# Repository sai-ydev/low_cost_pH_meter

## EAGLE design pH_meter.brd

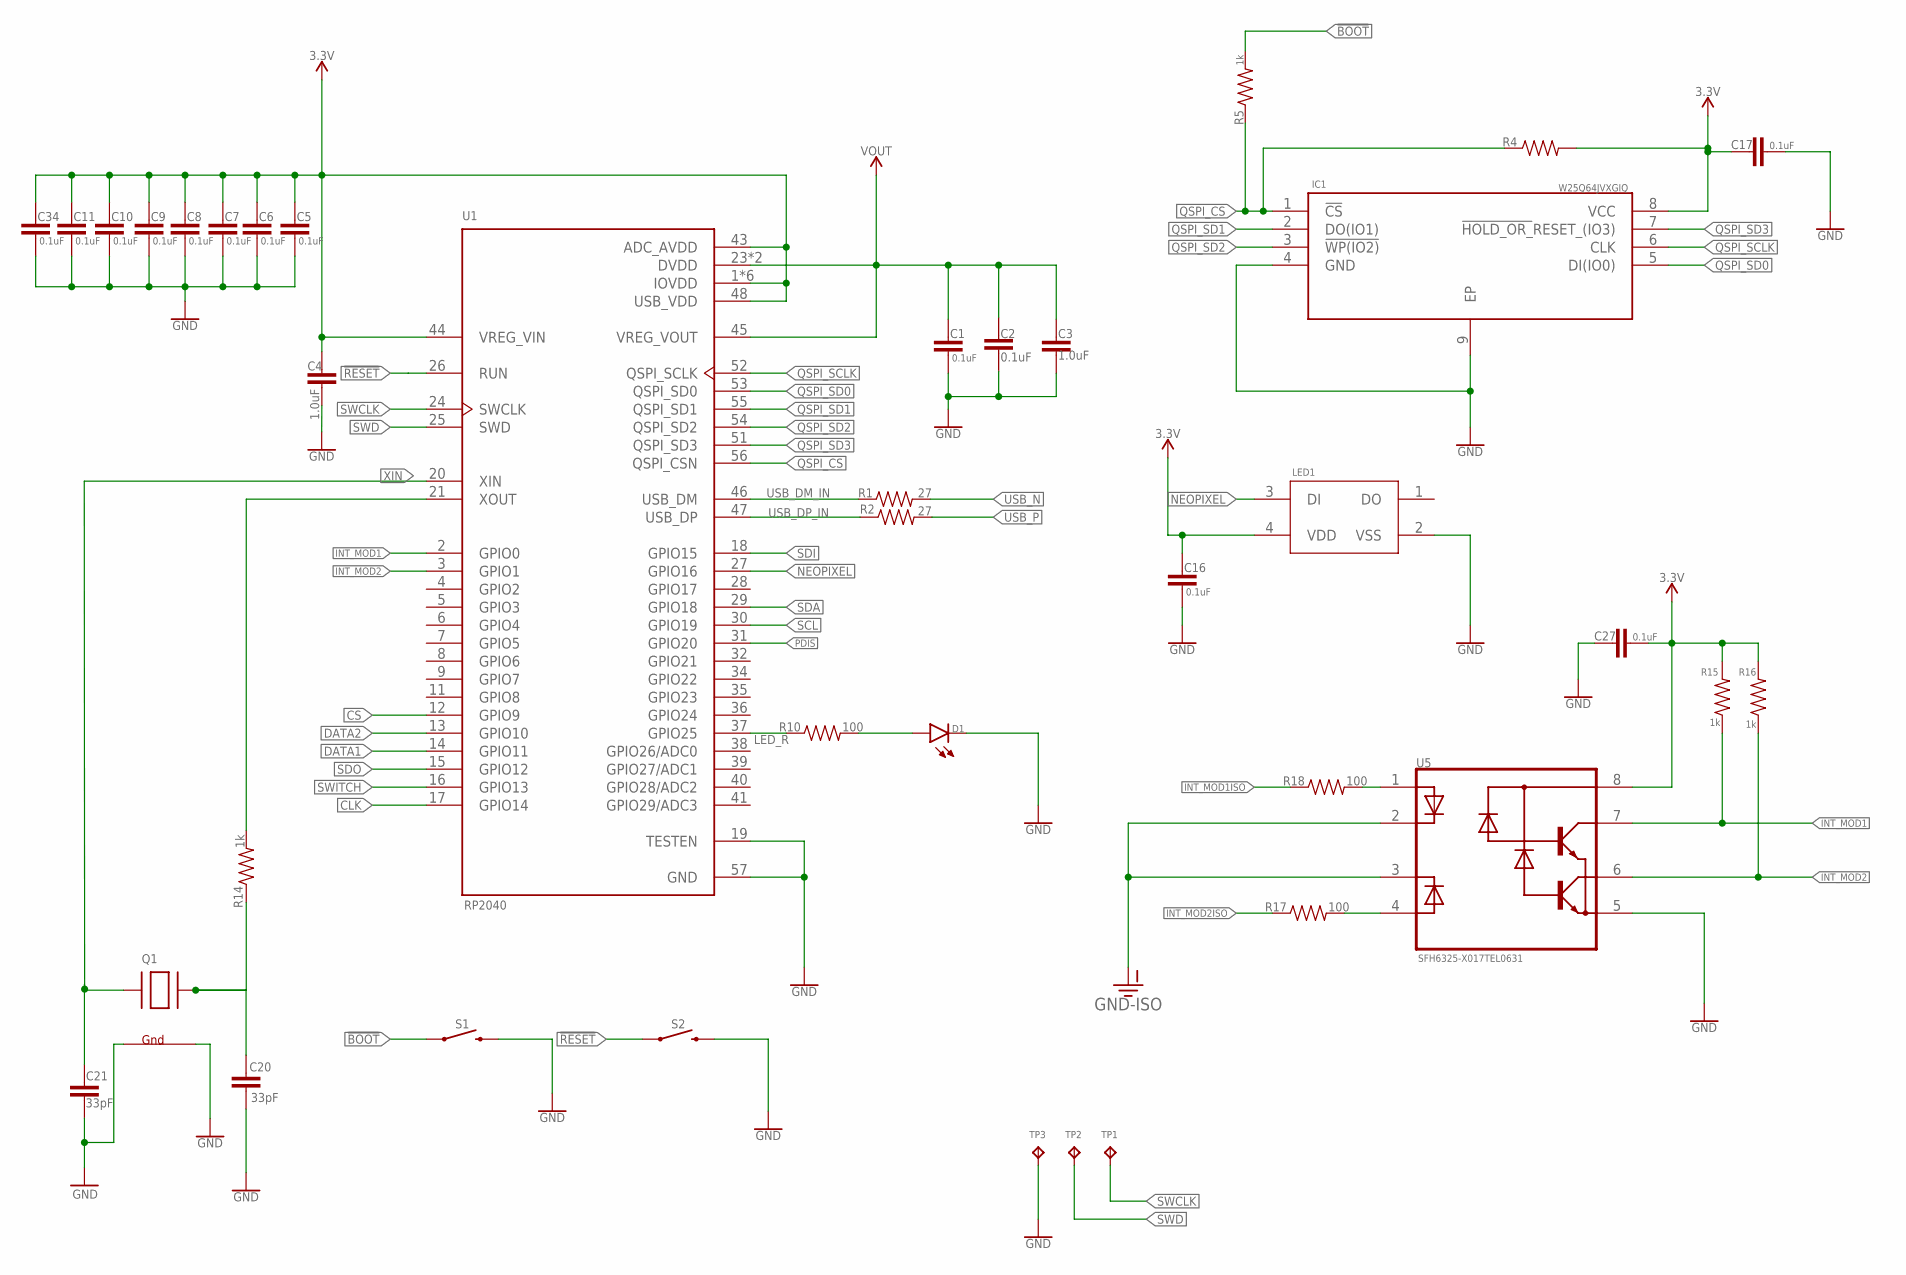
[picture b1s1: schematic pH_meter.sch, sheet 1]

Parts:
C1, C2, C5, C6, C7, C8, C9, C10, C11, C16, C17, C27, C34: 0.1uF; 0603
C3, C4: 1.0uF; 0603
C20, C21: 33pF; 0603
D1: LED0603; LED-0603
IC1: W25Q64JVXGIQ; SON80P400X400X50-9N
LED1: WS2812B-2020
Q1: XTAL-4-3225; NX3225
R1, R2: 27; 0603
R4: 0603
R5, R14, R15, R16: 1k; 0603
R10, R17, R18: 100; 0603
S1, S2: MOMENTARY-SWITCH-SPST-SMD-4.6X2.8MM; TACTILE_SWITCH_SMD_4.6X2.8MM
TP1, TP2, TP3: TPB2,54; B2,54
U1: RP2040; QFN40P700X700X90-57N
U5: SFH6325-X017TEL0631; SOIC127P599X175-8N

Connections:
3.3V: C4.1, C5.1, C6.1, C7.1, C8.1, C9.1, C10.1, C11.1, C16.1, C17.1, C27.2, C34.1, IC1.8 (VCC), LED1.4 (VDD), R4.2, R15.2, R16.2, U1.1 (IOVDD), U1.10 (IOVDD), U1.22 (IOVDD), U1.33 (IOVDD), U1.42 (IOVDD), U1.43 (ADC_AVDD), U1.44 (VREG_VIN), U1.48 (USB_VDD), U1.49 (IOVDD), U5.8 (C(VCC)); also elsewhere on the board
!BOOT: R5.2, S1.1, S1.2 (1)
!RESET: S2.1, S2.2 (1), U1.26 (RUN)
CLK: U1.17 (GPIO14); also elsewhere on the board
CS: U1.12 (GPIO9); also elsewhere on the board
DATA1: U1.14 (GPIO11); also elsewhere on the board
DATA2: U1.13 (GPIO10); also elsewhere on the board
GND: C1.2, C2.2, C3.2, C4.2, C5.2, C6.2, C7.2, C8.2, C9.2, C10.2, C11.2, C16.2, C17.2, C20.1, C21.1, C27.1, C34.2, D1.C, IC1.4 (GND), IC1.9 (EP), LED1.2 (VSS), Q1.2 (G2), Q1.4 (G1), S1.3 (2), S1.4 (2), S2.3 (2), S2.4 (2), TP3.TP, U1.19 (TESTEN), U1.57 (GND), U5.5 (E(GND)); also elsewhere on the board
GND-ISO: U5.2 (C1), U5.3 (C2); also elsewhere on the board
INT_MOD1: R15.1, U1.2 (GPIO0), U5.7 (C1(VO1))
INT_MOD1ISO: R18.1; also elsewhere on the board
INT_MOD2: R16.1, U1.3 (GPIO1), U5.6 (C2(VO2))
INT_MOD2ISO: R17.1; also elsewhere on the board
LED_R: R10.1, U1.37 (GPIO25)
unnamed: D1.A, R10.2
unnamed: C20.2, Q1.3 (X2), R14.1
unnamed: R14.2, U1.21 (XOUT)
unnamed: R17.2, U5.4 (A2)
unnamed: R18.2, U5.1 (A1)
NEOPIXEL: LED1.3 (DI), U1.27 (GPIO16)
PDIS: U1.31 (GPIO20); also elsewhere on the board
QSPI_CS: IC1.1 (!CS), R4.1, R5.1, U1.56 (QSPI_CSN)
QSPI_SCLK: IC1.6 (CLK), U1.52 (QSPI_SCLK)
QSPI_SD0: IC1.5 (DI(IO0)), U1.53 (QSPI_SD0)
QSPI_SD1: IC1.2 (DO(IO1)), U1.55 (QSPI_SD1)
QSPI_SD2: IC1.3 (!WP(IO2)), U1.54 (QSPI_SD2)
QSPI_SD3: IC1.7 (!HOLD_OR_!RESET_(IO3)), U1.51 (QSPI_SD3)
SCL: U1.30 (GPIO19); also elsewhere on the board
SDA: U1.29 (GPIO18); also elsewhere on the board
SDI: U1.18 (GPIO15); also elsewhere on the board
SDO: U1.15 (GPIO12); also elsewhere on the board
SWCLK: TP1.TP, U1.24 (SWCLK)
SWD: TP2.TP, U1.25 (SWD)
SWITCH: U1.16 (GPIO13); also elsewhere on the board
USB_DM_IN: R1.1, U1.46 (USB_DM)
USB_DP_IN: R2.1, U1.47 (USB_DP)
USB_N: R1.2; also elsewhere on the board
USB_P: R2.2; also elsewhere on the board
VOUT: C1.1, C2.1, C3.1, U1.23 (DVDD), U1.45 (VREG_VOUT), U1.50 (DVDD)
XIN: C21.2, Q1.1 (X1), U1.20 (XIN)

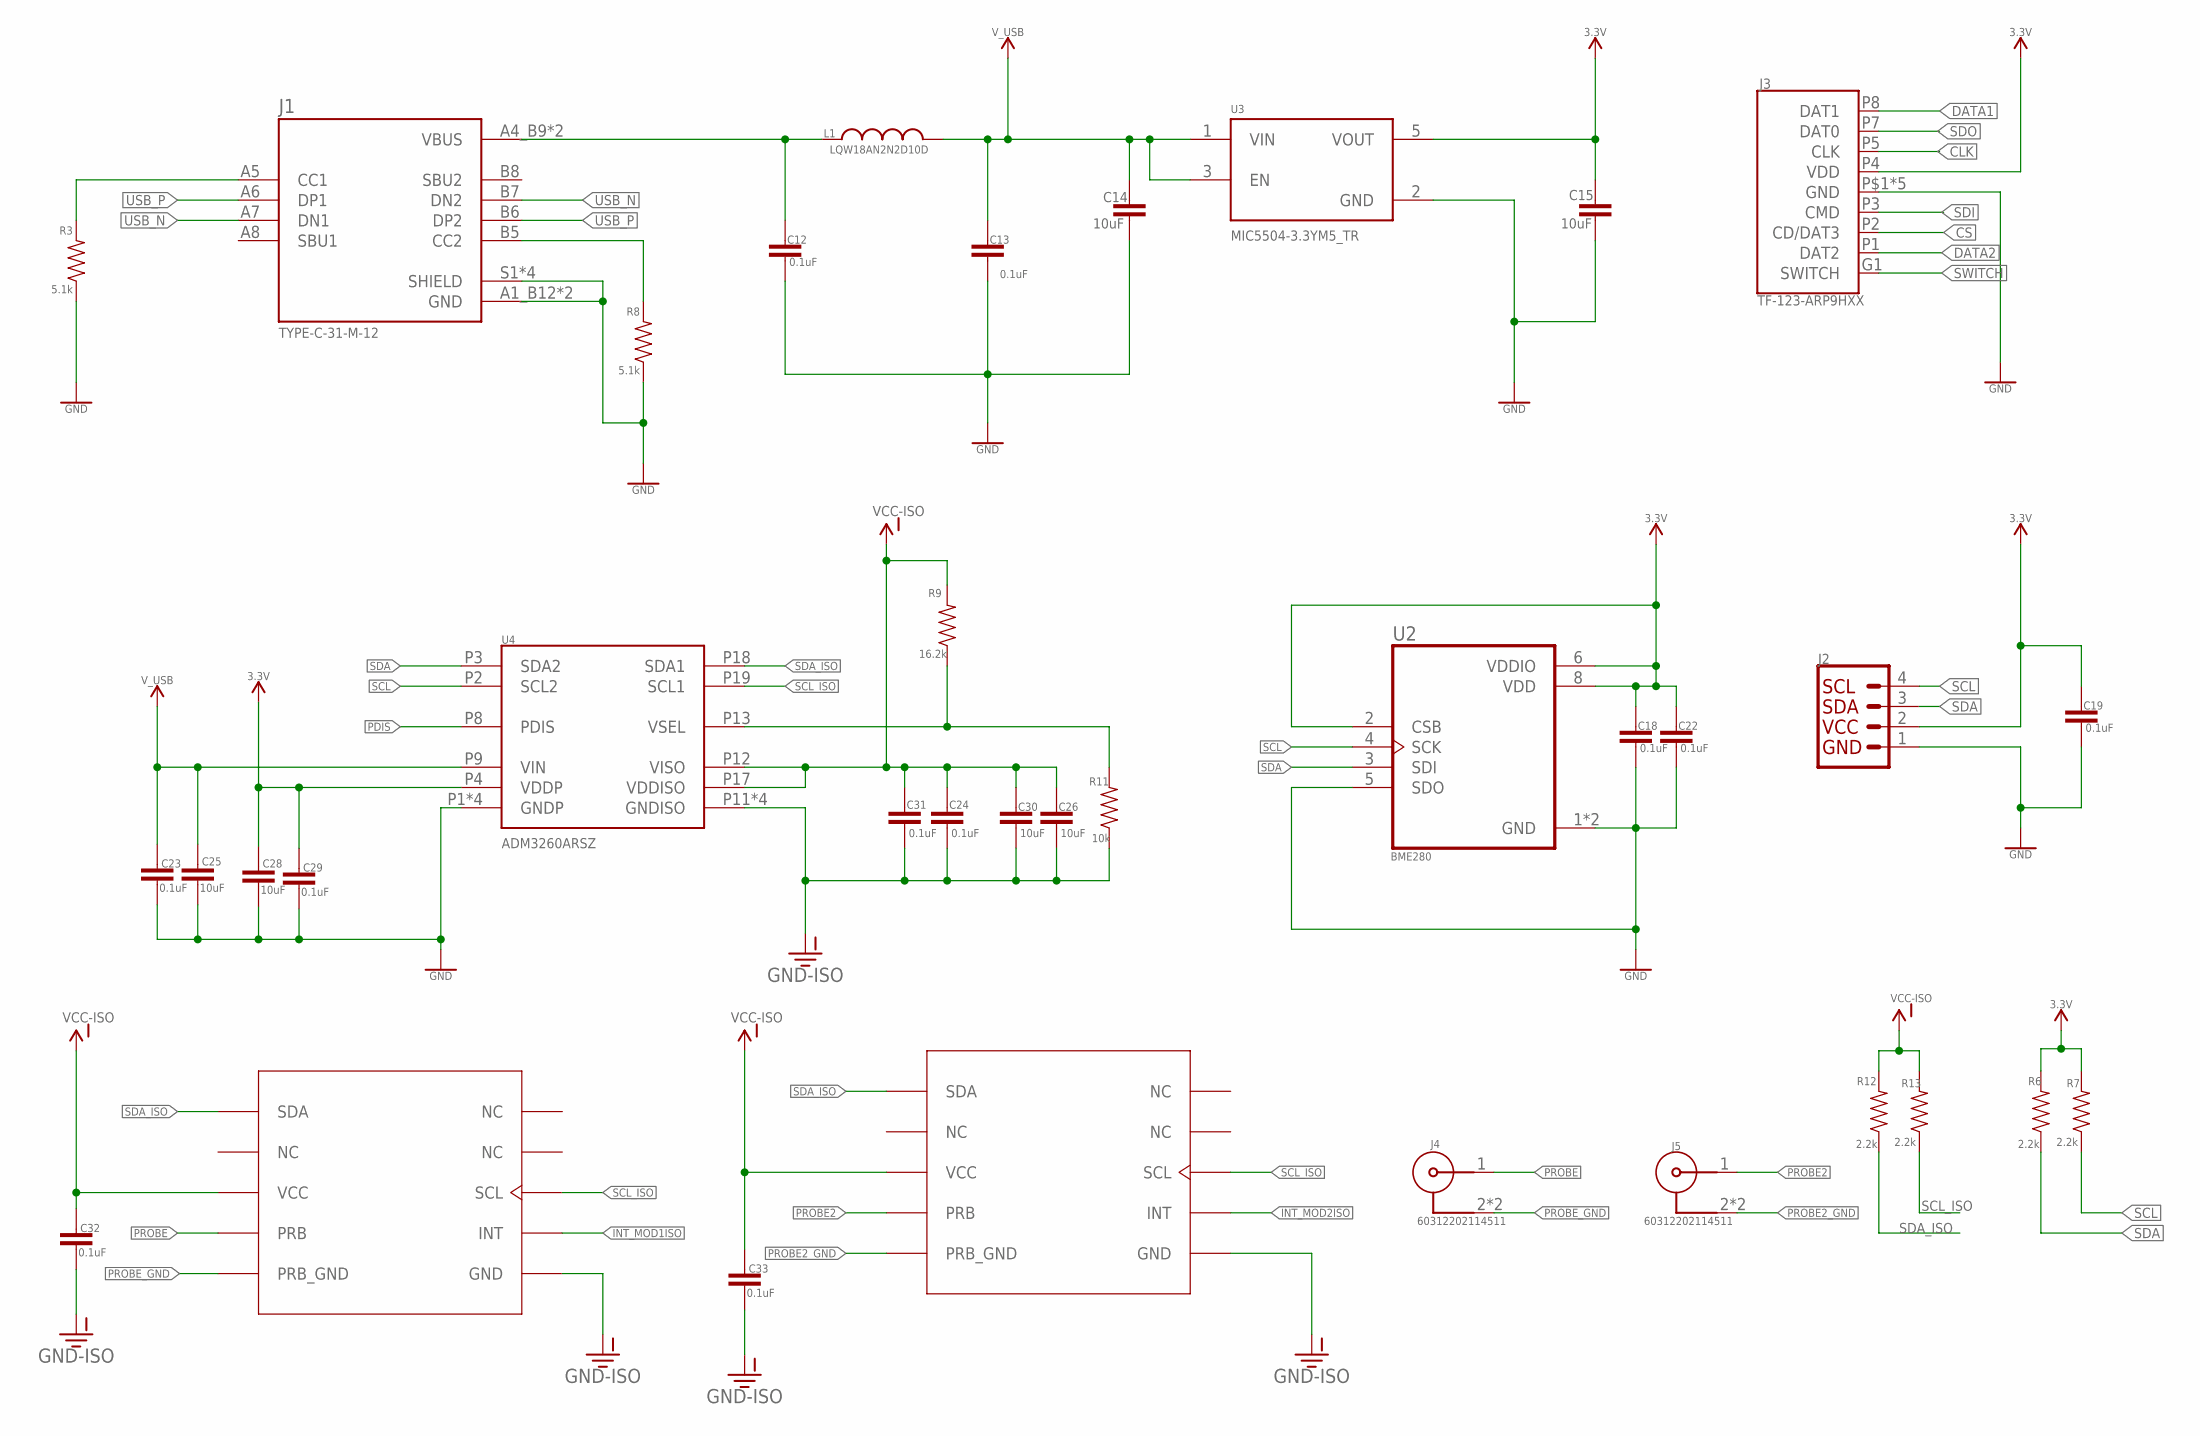
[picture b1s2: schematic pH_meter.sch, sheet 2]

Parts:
C12, C13, C18, C19, C22, C23, C24, C29, C31, C32, C33: 0.1uF; 0603
C14, C15, C25, C26, C28, C30: 10uF; 0603
J1: TYPE-C-31-M-12; HRO_TYPE-C-31-M-12
J2: QWIIC_CONNECTORJS-1MM; 1X04_1MM_RA
J3: TF-123-ARP9HXX; MICROSDCARD
J4, J5: 60312202114511
L1: LQW18AN2N2D10D; INDC1608X100N
R3, R8: 5.1k; 0603
R6, R7, R12, R13: 2.2k; 0603
R9: 16.2k; 0603
R11: 10k; 0603
U2: BME280; PSON65P250X250X100-8N
U3: MIC5504-3.3YM5_TR; SOT95P280X145-5N
U4: ADM3260ARSZ; SSOP20
U$1, U$2: PH-OEM; PH_SENSOR

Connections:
3.3V: C15.2, C18.1, C19.1, C22.1, C28.1, C29.1, J2.2, J3.P4 (VDD), R6.2, R7.2, U2.2 (CSB), U2.6 (VDDIO), U2.8 (VDD), U3.5 (VOUT), U4.P4 (VDDP); also elsewhere on the board
CLK: J3.P5 (CLK); also elsewhere on the board
CS: J3.P2 (CD/DAT3); also elsewhere on the board
DATA1: J3.P8 (DAT1); also elsewhere on the board
DATA2: J3.P1 (DAT2); also elsewhere on the board
GND: C12.2, C13.2, C14.1, C15.1, C18.2, C19.2, C22.2, C23.2, C25.2, C28.2, C29.2, J1.A1_B12 (GND), J1.B1_A12 (GND), J1.S1 (SHIELD), J1.S2 (SHIELD), J1.S3 (SHIELD), J1.S4 (SHIELD), J2.1, J3.P6 (GND), J3.P$1 (GND), J3.P$2 (GND), J3.P$3 (GND), J3.P$4 (GND), R3.1, R8.1, U2.1 (GND), U2.5 (SDO), U2.7 (GND), U3.2 (GND), U4.P1 (GNDP), U4.P5 (GNDP), U4.P7 (GNDP), U4.P10 (GNDP); also elsewhere on the board
GND-ISO: C24.2, C26.2, C30.2, C31.2, C32.2, C33.2, R11.1, U4.P11 (GNDISO), U4.P14 (GNDISO), U4.P16 (GNDISO), U4.P20 (GNDISO), U$1.P$6 (GND), U$2.P$6 (GND); also elsewhere on the board
INT_MOD1ISO: U$2.P$7 (INT); also elsewhere on the board
INT_MOD2ISO: U$1.P$7 (INT); also elsewhere on the board
unnamed: R9.1, R11.2, U4.P13 (VSEL)
unnamed: J1.A5 (CC1), R3.2
unnamed: J1.B5 (CC2), R8.2
unnamed: C12.1, J1.A4_B9 (VBUS), J1.B4_A9 (VBUS), L1.1
PDIS: U4.P8 (PDIS); also elsewhere on the board
PROBE: J4.1, U$2.P$4 (PRB)
PROBE2: J5.1, U$1.P$4 (PRB)
PROBE2_GND: J5.2, J5.3 (2), U$1.P$5 (PRB_GND)
PROBE_GND: J4.2, J4.3 (2), U$2.P$5 (PRB_GND)
SCL: J2.4, R7.1, U2.4 (SCK), U4.P2 (SCL2); also elsewhere on the board
SCL_ISO: R13.1, U4.P19 (SCL1), U$1.P$8 (SCL), U$2.P$8 (SCL)
SDA: J2.3, R6.1, U2.3 (SDI), U4.P3 (SDA2); also elsewhere on the board
SDA_ISO: R12.1, U4.P18 (SDA1), U$1.P$1 (SDA), U$2.P$1 (SDA)
SDI: J3.P3 (CMD); also elsewhere on the board
SDO: J3.P7 (DAT0); also elsewhere on the board
SWITCH: J3.G1 (SWITCH); also elsewhere on the board
USB_N: J1.A7 (DN1), J1.B7 (DN2); also elsewhere on the board
USB_P: J1.A6 (DP1), J1.B6 (DP2); also elsewhere on the board
VCC-ISO: C24.1, C26.1, C30.1, C31.1, C32.1, C33.1, R9.2, R12.2, R13.2, U4.P12 (VISO), U4.P17 (VDDISO), U$1.P$3 (VCC), U$2.P$3 (VCC)
V_USB: C13.1, C14.2, C23.1, C25.1, L1.2, U3.1 (VIN), U3.3 (EN), U4.P9 (VIN)

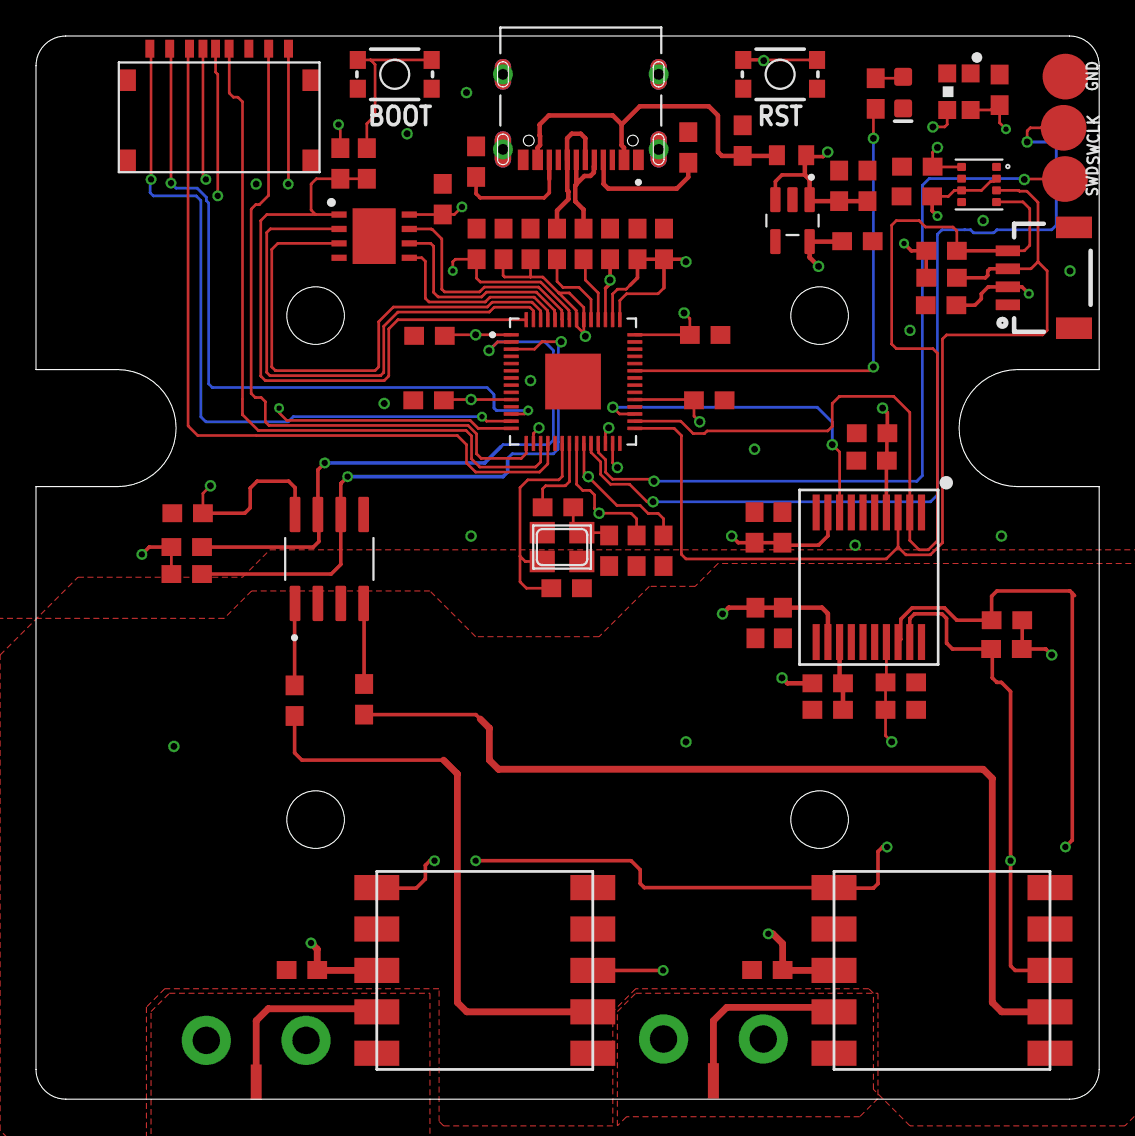
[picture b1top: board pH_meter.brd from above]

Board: 4 copper layers, 59.1 x 59.1 mm, 74 parts (0 on the bottom side), 52 nets.

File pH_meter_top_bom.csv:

Comment,Designator,Footprint,LCSC Part #
 ,D1 J2 Q1 R4,0603,
0.1uF,C1 C2 C5 C6 C7 C8 C9 C10 C11 C12 C13 C16 C17 C18 C19 C22 C23 C24 C27 C29 C31 C32 C33 C34,0603,
1.0uF,C3 C4,0603,
1k,R5 R14 R15 R16,0603,
2.2k,R6 R7 R12 R13,0603,
5.1k,R3 R8,0603,
10k,R11,0603,
10uF,C14 C15 C25 C26 C28 C30,0603,
16.2k,R9,0603,
27,R1 R2,0603,
33pF,C20 C21,0603,
100,R10 R17 R18,0603,
60312202114511,J4 J5,60312202114511,
ADM3260ARSZ,U4,SSOP20,
BME280,U2,PSON65P250X250X100-8N,
LQW18AN2N2D10D,L1,INDC1608X100N,
MIC5504-3.3YM5_TR,U3,SOT95P280X145-5N,
MOMENTARY-SWITCH-SPST-SMD-4.6X2.8MM,S1 S2,TACTILE_SWITCH_SMD_4.6X2.8MM,
PH-OEM,U$1 U$2,PH_SENSOR,
RP2040,U1,QFN40P700X700X90-57N,
SFH6325-X017TEL0631,U5,SOIC127P599X175-8N,
TF-123-ARP9HXX,J3,MICROSDCARD,
TPB2 54,TP1,B2 54,
TPB2 54,TP2,B2 54,
TPB2 54,TP3,B2 54,
TYPE-C-31-M-12,J1,HRO_TYPE-C-31-M-12,
W25Q64JVXGIQ,IC1,SON80P400X400X50-9N,
WS2812B-2020,LED1,WS2812B-2020,

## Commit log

2024-05-08 Design files check-in
2024-05-19 Daily check-in
2024-05-25 Partial component placement
2024-05-29 Generated gerbers
2024-05-31 Changes to accommodate BoM costs
2024-06-02 Updated gerber file checkin
    Removed old gerber files

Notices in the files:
parts and their libraries:
SparkFun-Capacitors: Licensing: Creative Commons ShareAlike 4.0 International - https://creativecommons.org/licenses/by-sa/4.0
